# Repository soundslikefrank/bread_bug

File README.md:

# bread_bug
A Eurorack power section as a breadboard module

## License

cc-by-sa-4.0

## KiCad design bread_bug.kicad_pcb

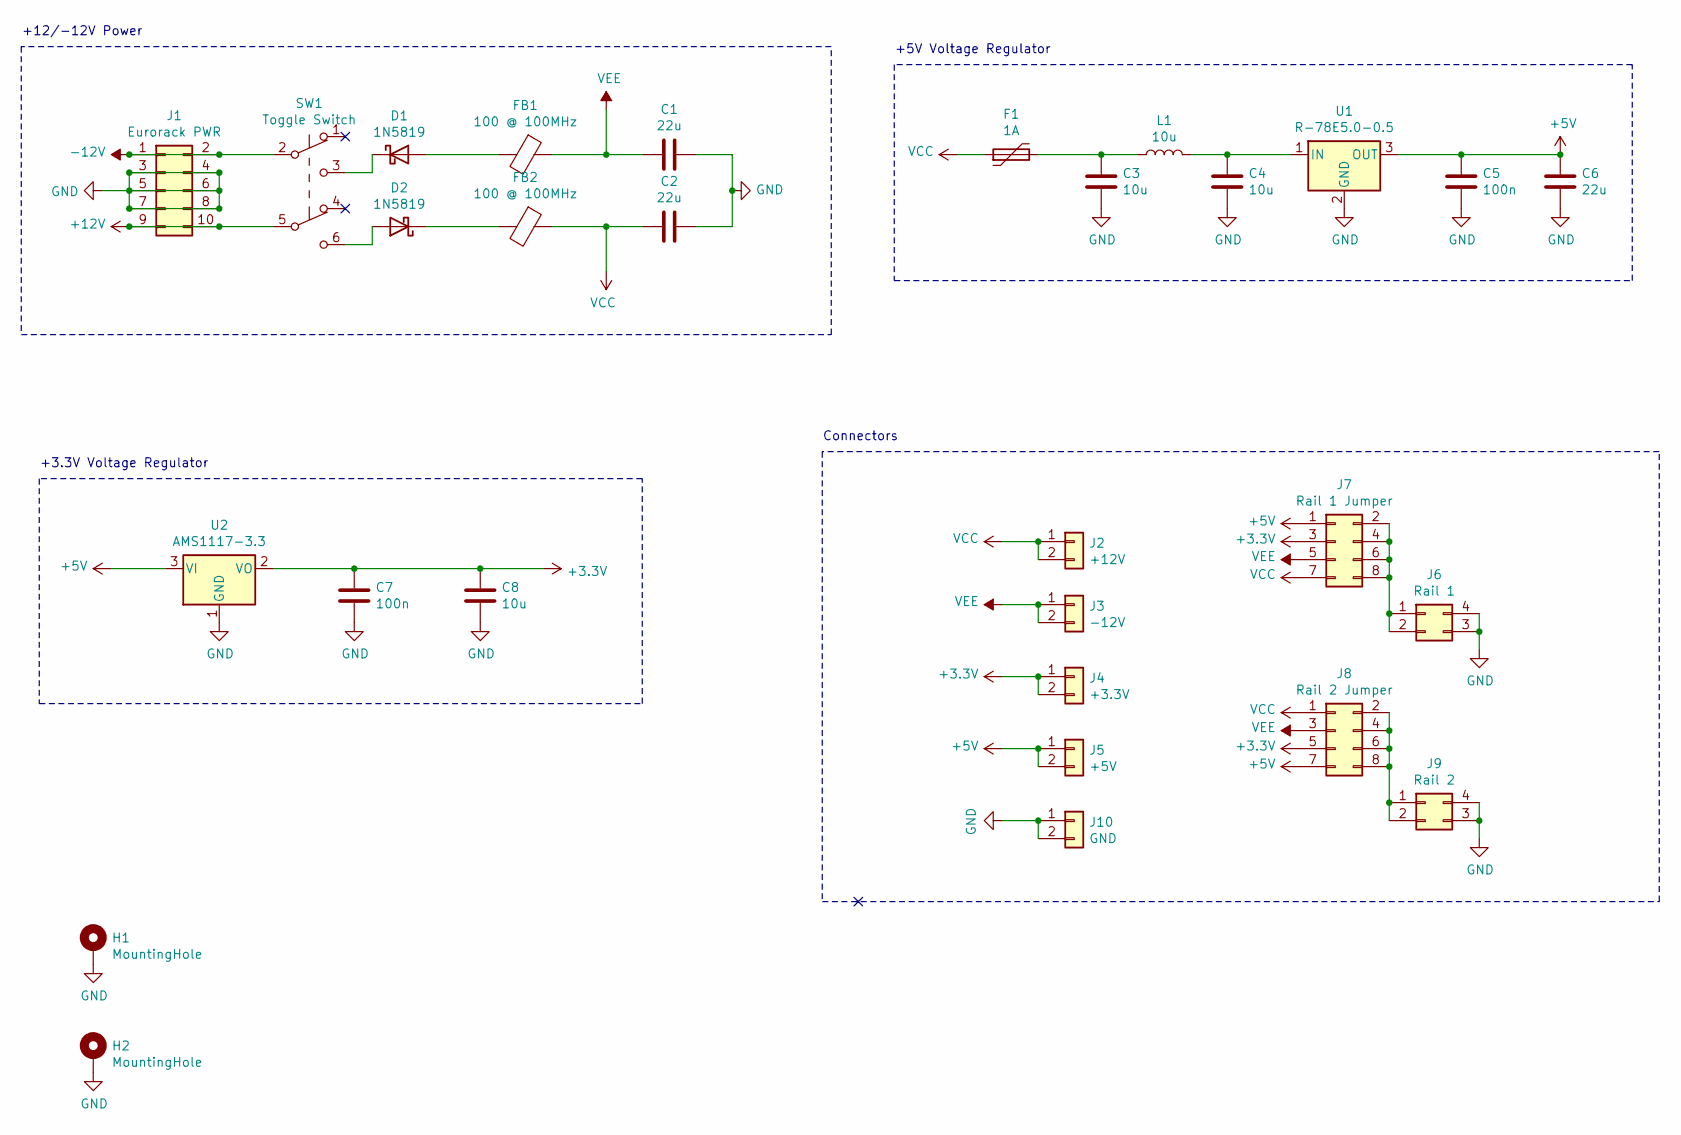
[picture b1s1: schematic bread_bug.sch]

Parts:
C1, C2, C6: 22u; C_0805_2012Metric_Pad1.15x1.40mm_HandSolder
C3, C4, C8: 10u; C_0805_2012Metric_Pad1.15x1.40mm_HandSolder
C5, C7: 100n; C_0805_2012Metric_Pad1.15x1.40mm_HandSolder
D1, D2: 1N5819; D_SOD-123
F1: 1A; Fuse_1206_3216Metric_Pad1.42x1.75mm_HandSolder
FB1, FB2: 100 @ 100MHz; L_0805_2012Metric_Pad1.15x1.40mm_HandSolder
H1, H2: MountingHole; MountingHole_3mm_Pad_Via
J1: Eurorack PWR; IDC-Header_2x05_P2.54mm_Vertical
J2: +12V; PinHeader_1x02_P2.54mm_Vertical
J3: -12V; PinHeader_1x02_P2.54mm_Vertical
J4: +3.3V; PinHeader_1x02_P2.54mm_Vertical
J5: +5V; PinHeader_1x02_P2.54mm_Vertical
J6: Rail 1; PinHeader_2x02_P2.54mm_Vertical
J7: Rail 1 Jumper; PinHeader_2x04_P2.54mm_Vertical
J8: Rail 2 Jumper; PinHeader_2x04_P2.54mm_Vertical
J9: Rail 2; PinHeader_2x02_P2.54mm_Vertical
J10: GND; PinHeader_1x02_P2.54mm_Vertical
L1: 10u; L_0805_2012Metric_Pad1.15x1.40mm_HandSolder
SW1: Toggle Switch; SW_TSM202A2
U1: R-78E5.0-0.5; Converter_DCDC_RECOM_R-78E-0.5_THT
U2: AMS1117-3.3; SOT-223-3_TabPin2

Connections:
+3V3: C7.1, C8.1, J4.1, J4.2, J7.3, J8.5, U2.2 (VO)
+5V: C5.1, C6.2, J5.1, J5.2, J7.1, J8.7, U1.3 (OUT), U2.3 (VI)
+12V: J1.9, J1.10, SW1.5 (B)
-12V: J1.1, J1.2, SW1.2 (B)
GND: C1.1, C2.1, C3.2, C4.1, C5.2, C6.1, C7.2, C8.2, H1.1, H2.1, J1.3, J1.4, J1.5, J1.6, J1.7, J1.8, J6.3, J6.4, J9.3, J9.4, J10.1, J10.2, U1.2 (GND), U2.1 (GND); also elsewhere on the board
unnamed: C3.1, F1.2, L1.1
unnamed: C4.2, L1.2, U1.1 (IN)
unnamed: D1.1 (K), SW1.3 (C)
unnamed: D1.2 (A), FB1.2
unnamed: D2.1 (K), FB2.2
unnamed: D2.2 (A), SW1.6 (C)
unnamed: J6.1, J6.2, J7.2, J7.4, J7.6, J7.8
unnamed: J8.2, J8.4, J8.6, J8.8, J9.1, J9.2
VCC: C2.2, F1.1, FB2.1, J2.1, J2.2, J7.7, J8.1
VEE: C1.2, FB1.1, J3.1, J3.2, J7.5, J8.3

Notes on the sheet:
+12/-12V Power
+5V Voltage Regulator
+3.3V Voltage Regulator
Connectors

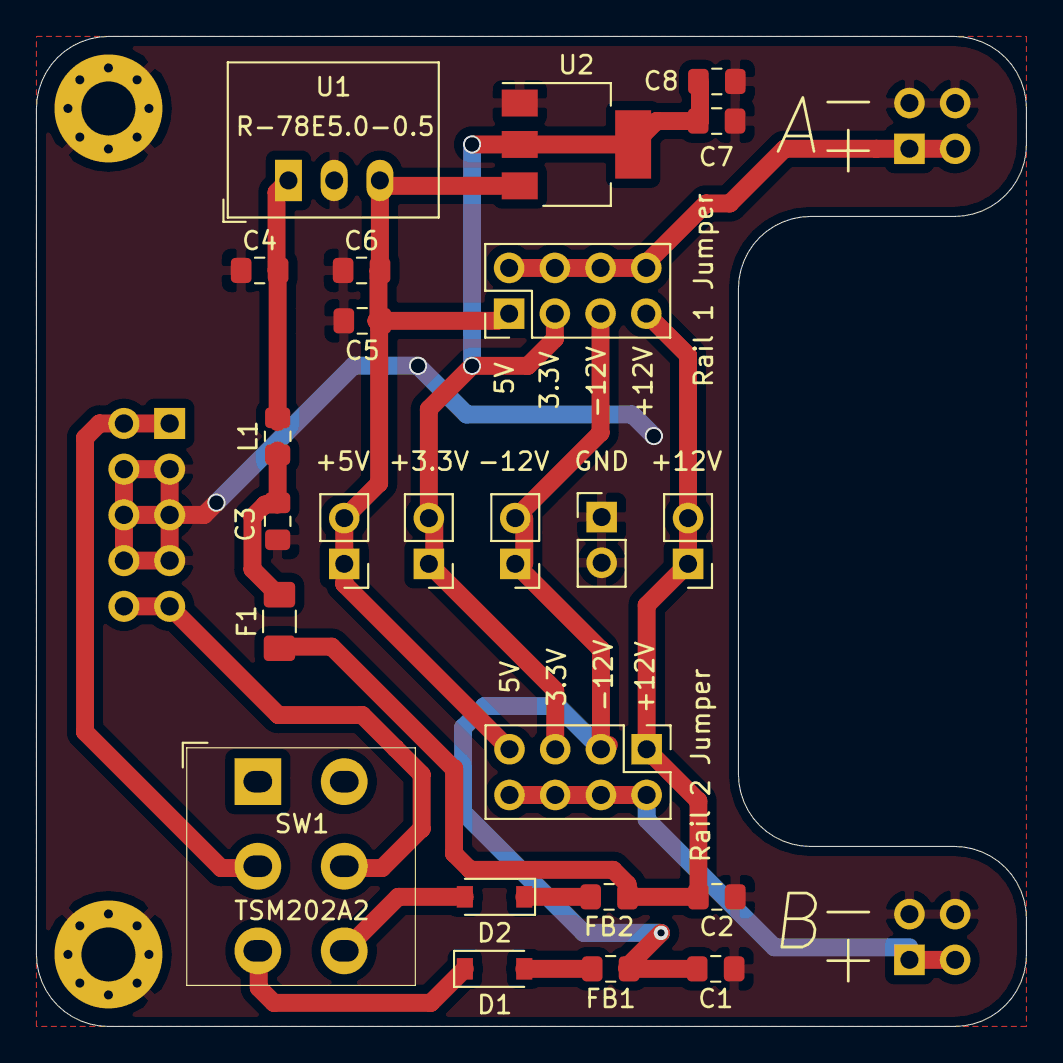
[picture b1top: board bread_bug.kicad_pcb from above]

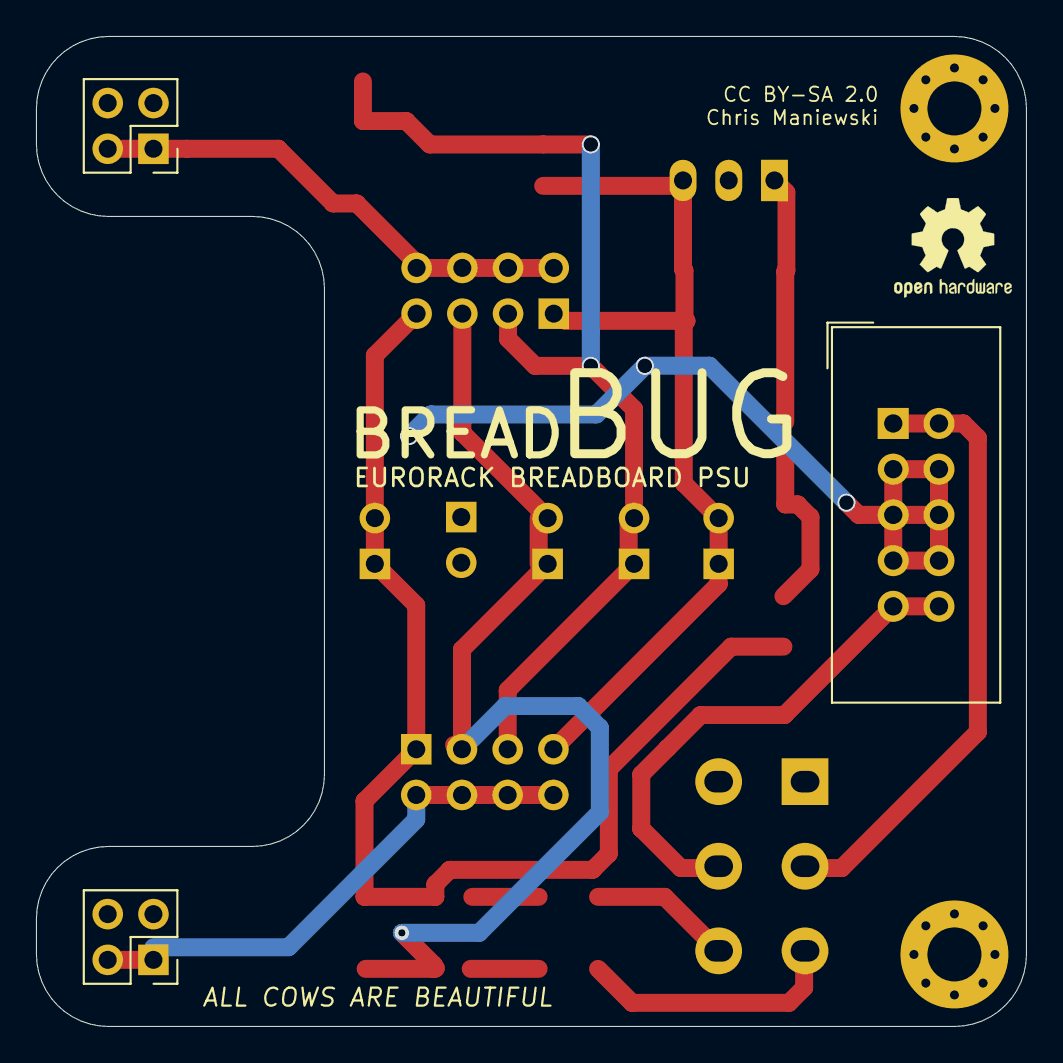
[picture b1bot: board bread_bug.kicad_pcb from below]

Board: 2 copper layers, 55.0 x 55.0 mm, 29 parts (3 on the bottom side), 15 nets.

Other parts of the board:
GND: GND; PinHeader_1x02_P2.54mm_Vertical

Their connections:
GND: GND.1, GND.2; also elsewhere on the board

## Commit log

2020-12-28 Remove gerber files from repo
2020-12-28 Rename to Bread Bug
2020-12-28 Add proper gitignore

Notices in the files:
bread_bug.kicad_pcb:
CC BY-SA 2.0
